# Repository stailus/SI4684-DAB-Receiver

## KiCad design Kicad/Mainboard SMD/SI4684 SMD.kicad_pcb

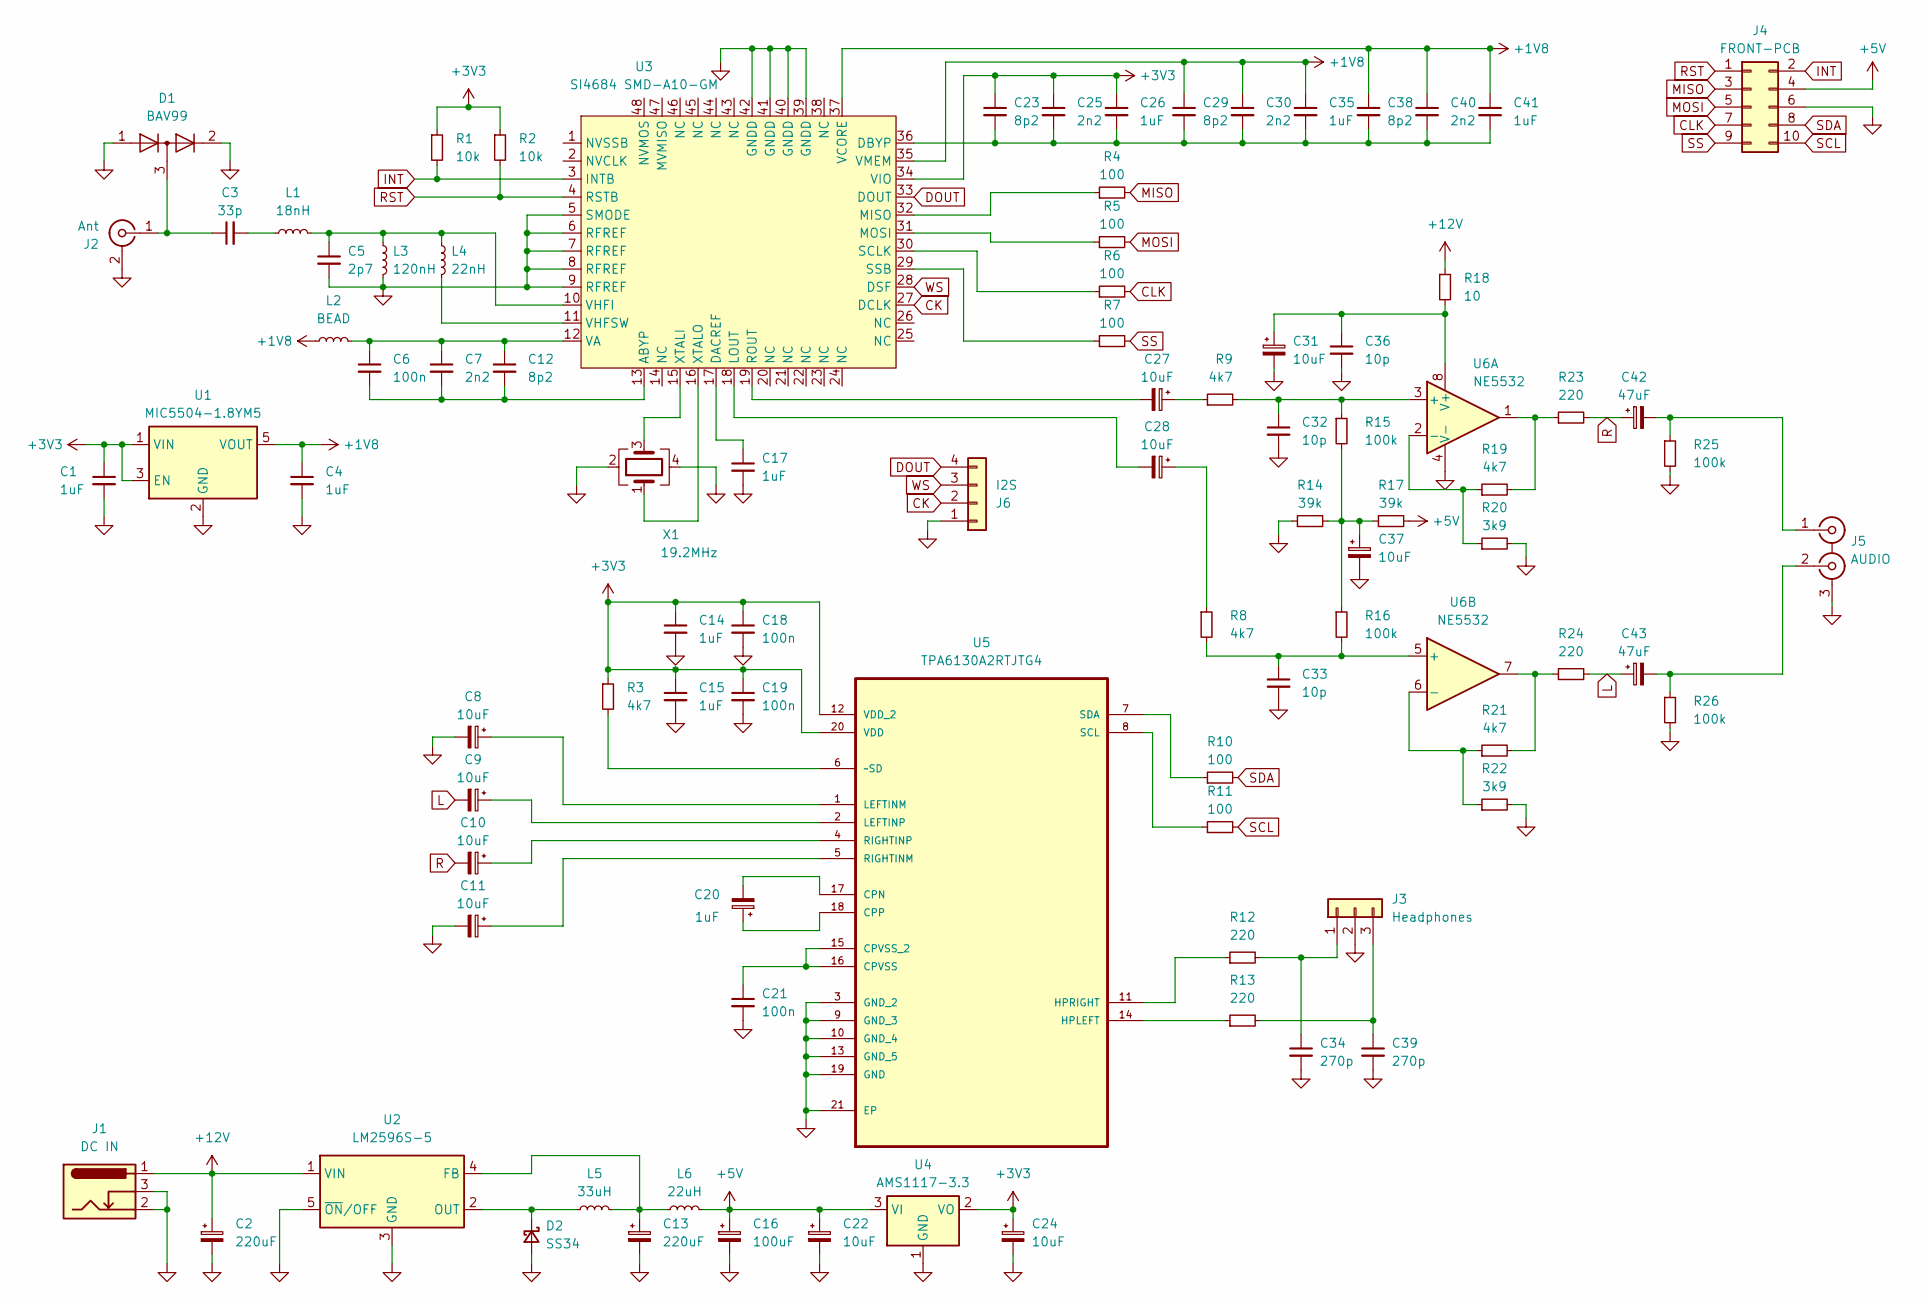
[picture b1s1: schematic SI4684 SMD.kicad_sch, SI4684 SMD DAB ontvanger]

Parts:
C1, C4, C14, C15, C17, C26, C35, C41: 1uF; C_0603_1608Metric
C2, C13: 220uF; CP_Elec_6.3x7.7
C3: 33p; C_0603_1608Metric
C5: 2p7; C_0603_1608Metric
C6, C18, C19, C21: 100n; C_0603_1608Metric
C7, C25, C30, C40: 2n2; C_0603_1608Metric
C8, C9, C10, C11, C22, C24, C27, C28, C31, C37: 10uF; CP_Elec_4x5.4
C12, C23, C29, C38: 8p2; C_0603_1608Metric
C16: 100uF; CP_Elec_6.3x7.7
C20: 1uF; CP_Elec_4x5.4
C32, C33, C36: 10p; C_0603_1608Metric
C34, C39: 270p; C_0603_1608Metric
C42, C43: 47uF; CP_Elec_6.3x5.4
D1: BAV99; SOT-23
D2: SS34; D_SMB
J1: DC IN; BarrelJack_Horizontal
J2: Ant; SMA_Amphenol_132134-16_Vertical
J3: Headphones; JST_PH_B3B-PH-K_1x03_P2.00mm_Vertical
J4: FRONT-PCB; IDC-Header_2x05_P2.54mm_Vertical
J5: AUDIO; FC68405_cinch
J6: I2S; PinHeader_1x04_P2.54mm_Vertical
L1: 18nH; L_0603_1608Metric
L2: BEAD; L_0603_1608Metric
L3: 120nH; L_0603_1608Metric
L4: 22nH; L_0603_1608Metric
L5: 33uH; L_TracoPower_TCK-047_5.2x5.8mm
L6: 22uH; L_TracoPower_TCK-047_5.2x5.8mm
R1, R2: 10k; R_0603_1608Metric
R3, R8, R9, R19, R21: 4k7; R_0603_1608Metric
R4, R5, R6, R7, R10, R11: 100; R_0603_1608Metric
R12, R13, R23, R24: 220; R_0603_1608Metric
R14, R17: 39k; R_0603_1608Metric
R15, R16, R25, R26: 100k; R_0603_1608Metric
R18: 10; R_0603_1608Metric
R20, R22: 3k9; R_0603_1608Metric
U1: MIC5504-1.8YM5; SOT-23-5
U2: LM2596S-5; TO-263-5_TabPin3
U3: SI4684 SMD-A10-GM; QFN-48-1EP_7x7mm_P0.5mm_EP5.3x5.3mm
U4: AMS1117-3.3; SOT-223-3_TabPin2
U5: TPA6130A2RTJTG4; QFN-20-1EP_4x4mm_P0.5mm_EP2.7x2.7mm; MPN TPA6130A2RTJTG4
U6: NE5532; SOIC-8_3.9x4.9mm_P1.27mm
X1: 19.2MHz; Crystal_SMD_3225-4Pin_3.2x2.5mm

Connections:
+1V8: C4.1, C29.1, C30.1, C35.1, C38.1, C40.1, C41.1, L2.1, U1.5 (VOUT), U3.35 (VMEM), U3.37 (VCORE)
+3V3: C1.1, C14.1, C15.1, C18.1, C19.1, C23.1, C24.1, C25.1, C26.1, R1.1, R2.1, R3.1, U1.1 (VIN), U1.3 (EN), U3.34 (VIO), U4.2 (VO), U5.12 (VDD_2), U5.20 (VDD)
+5V: C16.1, C22.1, J4.4, L6.2, R17.2, U4.3 (VI)
+12V: C2.1, J1.1, R18.1, U2.1 (VIN)
CK: J6.2, U3.27 (DCLK)
CLK: J4.7, R6.2
DOUT: J6.4, U3.33 (DOUT)
GND: C1.2, C2.2, C4.2, C5.2, C8.2, C11.2, C13.2, C14.2, C15.2, C16.2, C17.2, C18.2, C19.2, C21.2, C22.2, C24.2, C31.2, C32.2, C33.2, C34.2, C36.2, C37.2, C39.2, D1.1 (K), D1.2 (A), D2.2 (A), J1.2, J1.3, J2.2 (Ext), J3.2, J4.6, J5.3 (EXT), J6.1, L3.2, R14.1, R20.2, R22.2, R25.2, R26.2, U1.2 (GND), U2.3 (GND), U2.5 (~ON/OFF), U3.5 (SMODE), U3.6 (RFREF), U3.7 (RFREF), U3.8 (RFREF), U3.9 (RFREF), U3.39 (GNDD), U3.40 (GNDD), U3.41 (GNDD), U3.42 (GNDD), U3.49 (GND), U4.1 (GND), U5.3 (GND_2), U5.9 (GND_3), U5.10 (GND_4), U5.13 (GND_5), U5.19 (GND), U5.21 (EP), U6.4 (V-), X1.2, X1.4
INT: J4.2, R1.2, U3.3 (INTB)
L: C9.2, C43.1, R24.2
MISO: J4.3, R4.2
MOSI: J4.5, R5.2
unnamed: C3.2, L1.1
unnamed: C27.1, R9.1
unnamed: C28.1, R8.1
unnamed: C37.1, R14.2, R15.2, R16.1, R17.1
unnamed: D2.1 (K), L5.1, U2.2 (OUT)
unnamed: C3.1, D1.3 (K), J2.1 (In)
unnamed: C34.1, J3.1, R12.2
unnamed: C39.1, J3.3, R13.2
unnamed: C42.2, J5.1 (IN1), R25.1
unnamed: C43.2, J5.2 (IN2), R26.1
unnamed: R19.2, R23.1, U6.1
unnamed: R21.2, R24.1, U6.7
unnamed: C13.1, L5.2, L6.1, U2.4 (FB)
unnamed: C6.2, C7.2, C12.2, U3.13 (ABYP)
unnamed: C17.1, U3.17 (DACREF)
unnamed: C23.2, C25.2, C26.2, C29.2, C30.2, C35.2, C38.2, C40.2, C41.2, U3.36 (DBYP)
unnamed: C28.2, U3.18 (LOUT)
unnamed: R4.1, U3.32 (MISO)
unnamed: R5.1, U3.31 (MOSI)
unnamed: C27.2, U3.19 (ROUT)
unnamed: R6.1, U3.30 (SCLK)
unnamed: R7.1, U3.29 (SSB)
unnamed: C6.1, C7.1, C12.1, L2.2, U3.12 (VA)
unnamed: C5.1, L1.2, L3.1, L4.1, U3.10 (VHFI)
unnamed: L4.2, U3.11 (VHFSW)
unnamed: U3.15 (XTALI), X1.3
unnamed: U3.16 (XTALO), X1.1
unnamed: C20.2, U5.17 (CPN)
unnamed: C20.1, U5.18 (CPP)
unnamed: C21.1, U5.15 (CPVSS_2), U5.16 (CPVSS)
unnamed: R13.1, U5.14 (HPLEFT)
unnamed: R12.1, U5.11 (HPRIGHT)
unnamed: C8.1, U5.1 (LEFTINM)
unnamed: C9.1, U5.2 (LEFTINP)
unnamed: C11.1, U5.5 (RIGHTINM)
unnamed: C10.1, U5.4 (RIGHTINP)
unnamed: R11.1, U5.8 (SCL)
unnamed: R10.1, U5.7 (SDA)
unnamed: R3.2, U5.6 (~SD)
unnamed: C32.1, R9.2, R15.1, U6.3 (+)
unnamed: R19.1, R20.1, U6.2 (-)
unnamed: C33.1, R8.2, R16.2, U6.5 (+)
unnamed: R21.1, R22.1, U6.6 (-)
unnamed: C31.1, C36.1, R18.2, U6.8 (V+)
R: C10.2, C42.1, R23.2
RST: J4.1, R2.2, U3.4 (RSTB)
SCL: J4.10, R11.2
SDA: J4.8, R10.2
SS: J4.9, R7.2
WS: J6.3, U3.28 (DSF)

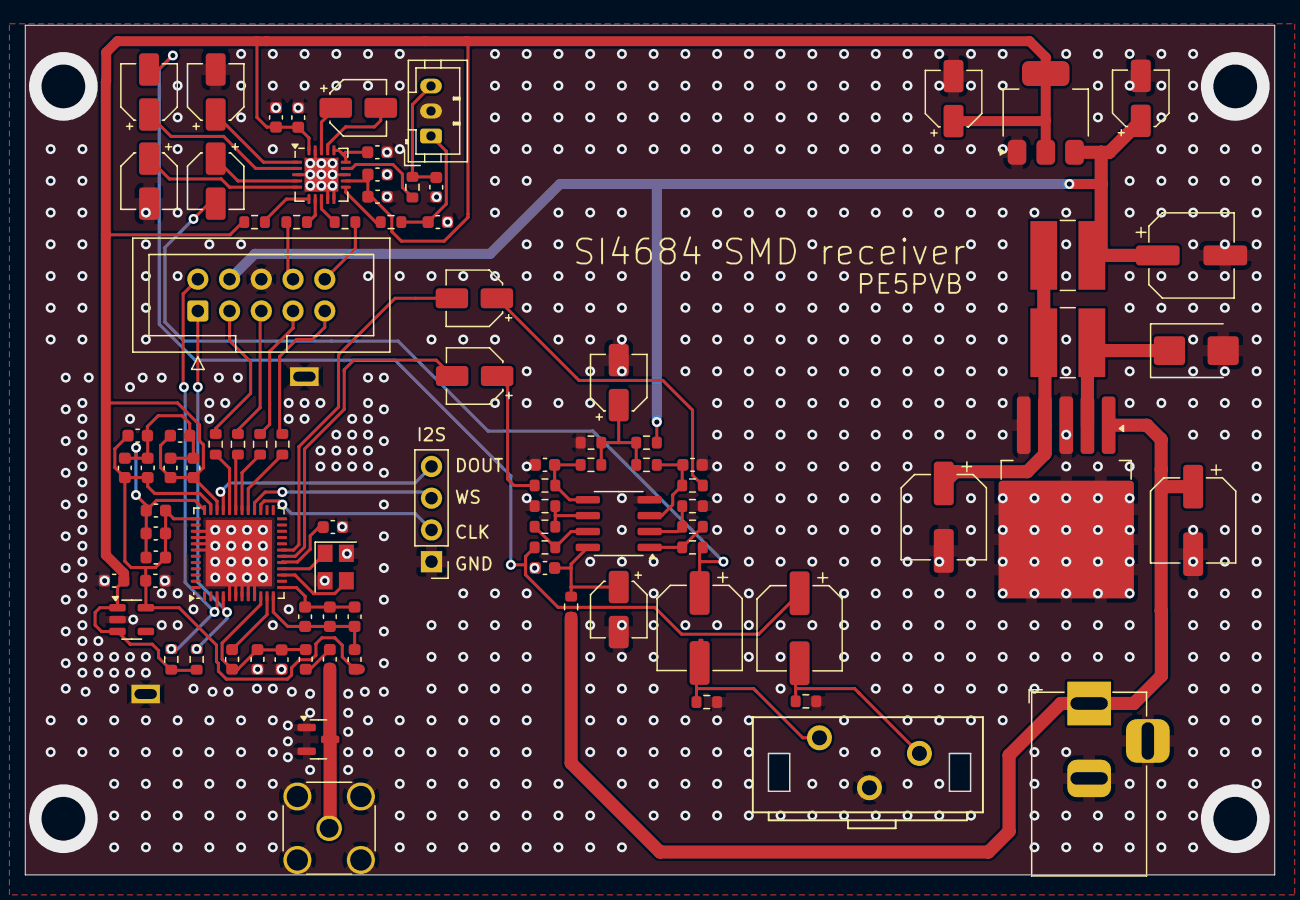
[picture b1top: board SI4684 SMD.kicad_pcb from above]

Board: 2 copper layers, 100.0 x 68.0 mm, 90 parts (0 on the bottom side), 62 nets.

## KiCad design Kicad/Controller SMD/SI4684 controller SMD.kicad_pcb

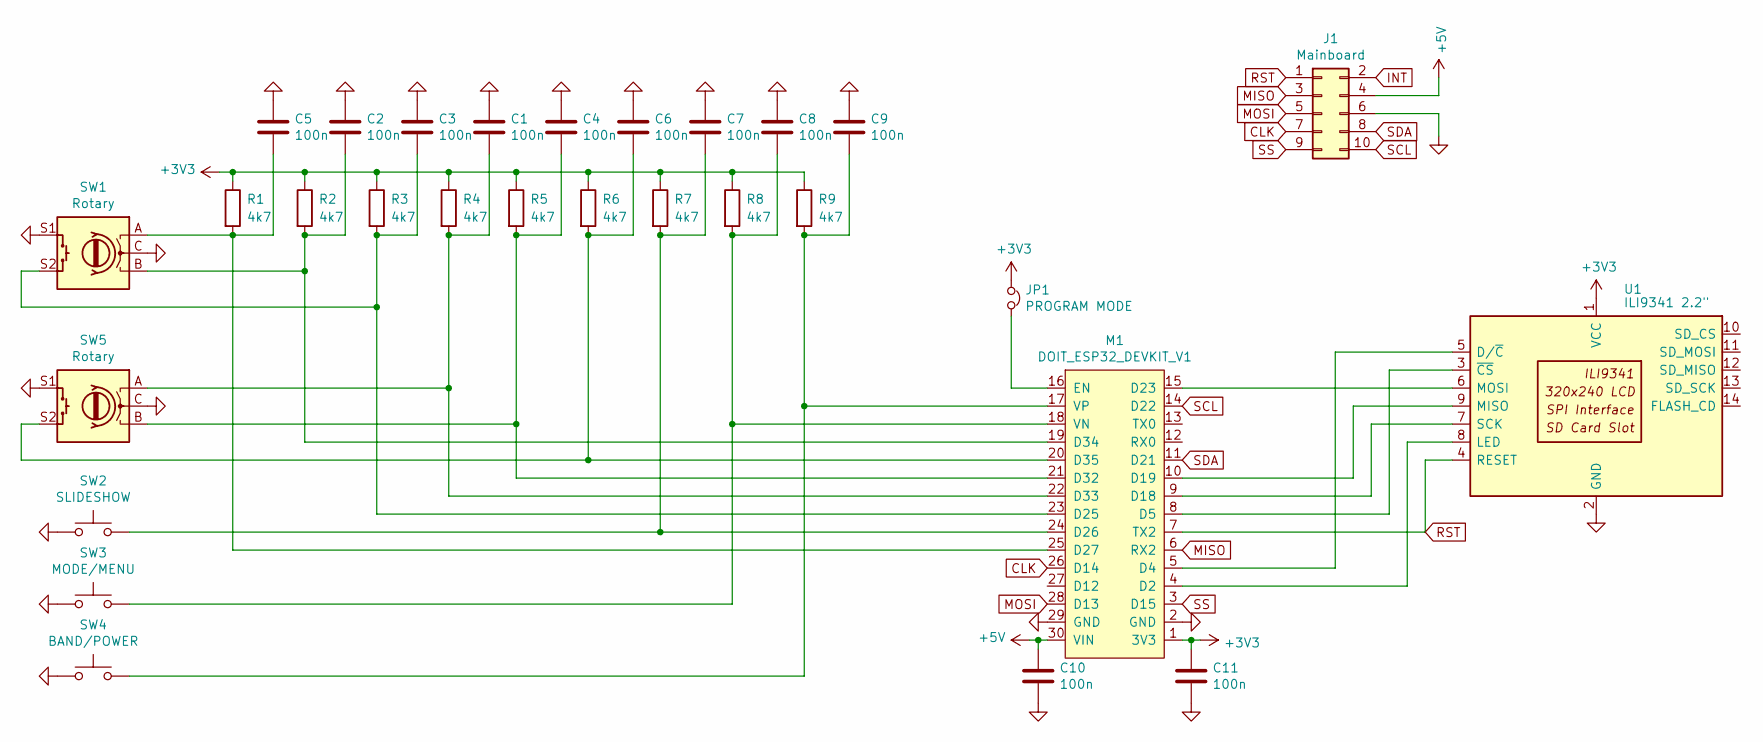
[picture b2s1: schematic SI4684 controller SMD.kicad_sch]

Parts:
C1, C2, C3, C4, C5, C6, C7, C8, C9, C10, C11: 100n; C_0603_1608Metric
J1: Mainboard; IDC-Header_2x05_P2.54mm_Vertical
JP1: PROGRAM MODE; TestPoint_2Pads_Pitch2.54mm_Drill0.8mm
M1: DOIT_ESP32_DEVKIT_V1; ESP32_DOIT_DEVKIT_V1
R1, R2, R3, R4, R5, R6, R7, R8, R9: 4k7; R_0603_1608Metric
SW1, SW5: Rotary; RotaryEncoder_Alps_EC11E-Switch_Vertical_H20mm
SW2: SLIDESHOW; SW_PUSH_6mm_H7.3mm
SW3: MODE/MENU; SW_PUSH_6mm_H7.3mm
SW4: BAND/POWER; SW_PUSH_6mm_H7.3mm
U1: ILI9341 2.2"; CR2013-MI2120

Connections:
+3V3: C11.1, JP1.1, M1.1 (3V3), R1.1, R2.1, R3.1, R4.1, R5.1, R6.1, R7.1, R8.1, R9.1, U1.1 (VCC)
+5V: C10.1, J1.4, M1.30 (VIN)
CLK: J1.7, M1.26 (D14)
GND: C1.1, C2.1, C3.1, C4.1, C5.1, C6.1, C7.1, C8.1, C9.1, C10.2, C11.2, J1.6, M1.2 (GND), M1.29 (GND), SW1.C, SW1.S1, SW2.1, SW3.1, SW4.1, SW5.C, SW5.S1, U1.2 (GND)
INT: J1.2
MISO: J1.3, M1.6 (RX2)
MOSI: J1.5, M1.28 (D13)
unnamed: M1.4 (D2), U1.8 (LED)
unnamed: M1.5 (D4), U1.5 (D/~C)
unnamed: M1.8 (D5), U1.3 (~CS)
unnamed: M1.9 (D18), U1.7 (SCK)
unnamed: M1.10 (D19), U1.9 (MISO)
unnamed: M1.15 (D23), U1.6 (MOSI)
unnamed: C3.2, M1.23 (D25), R3.2, SW1.S2
unnamed: C7.2, M1.24 (D26), R7.2, SW2.2
unnamed: C5.2, M1.25 (D27), R1.2, SW1.A
unnamed: C4.2, M1.21 (D32), R5.2, SW5.B
unnamed: C1.2, M1.22 (D33), R4.2, SW5.A
unnamed: C2.2, M1.19 (D34), R2.2, SW1.B
unnamed: C6.2, M1.20 (D35), R6.2, SW5.S2
unnamed: JP1.2, M1.16 (EN)
unnamed: C8.2, M1.18 (VN), R8.2, SW3.2
unnamed: C9.2, M1.17 (VP), R9.2, SW4.2
RST: J1.1, M1.7 (TX2), U1.4 (RESET)
SCL: J1.10, M1.14 (D22)
SDA: J1.8, M1.11 (D21)
SS: J1.9, M1.3 (D15)

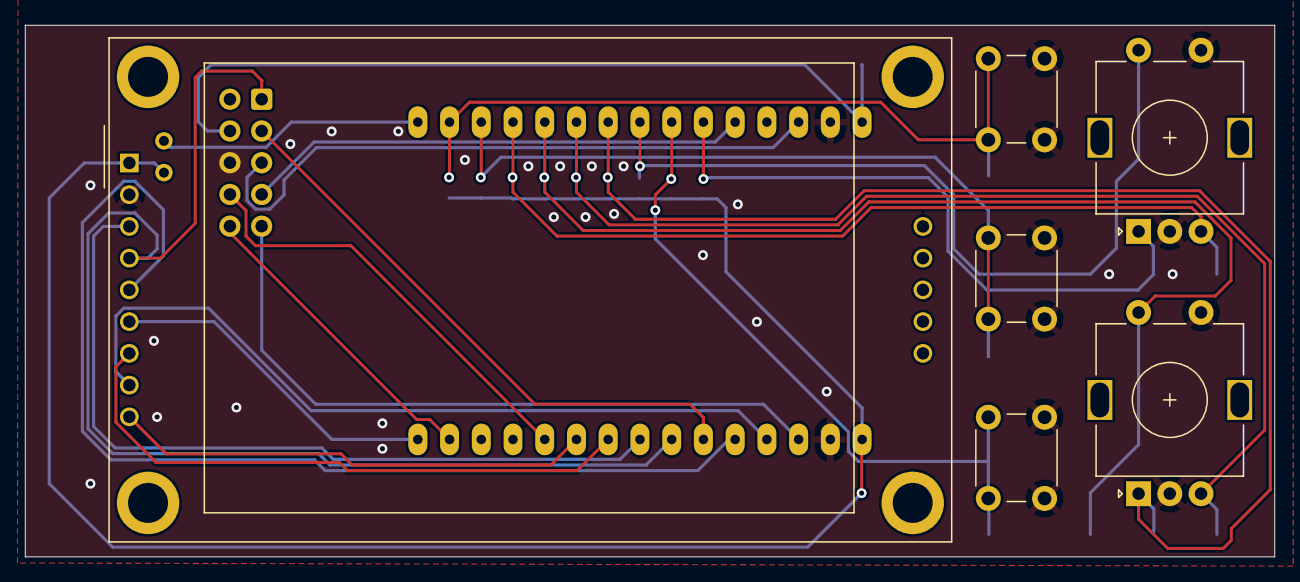
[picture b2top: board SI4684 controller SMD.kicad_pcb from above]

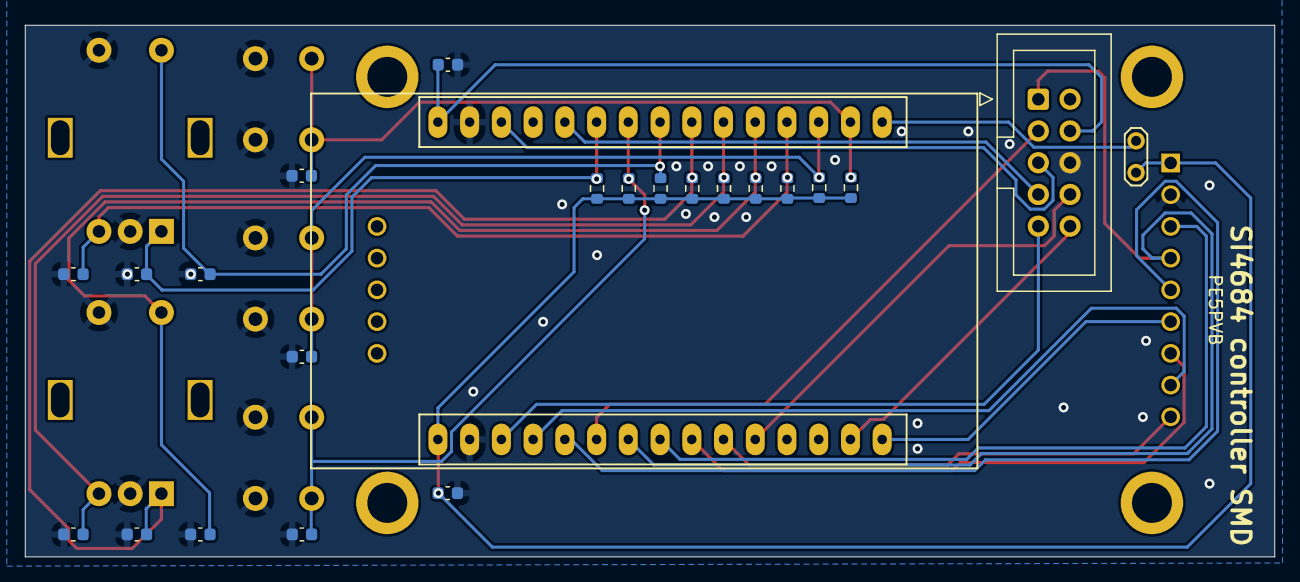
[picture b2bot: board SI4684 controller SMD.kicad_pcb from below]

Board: 2 copper layers, 100.0 x 42.5 mm, 29 parts (23 on the bottom side), 26 nets.

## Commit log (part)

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2025-07-09 Added SMD board Kicad files
2025-12-29 Fixed problem with compiling slideshow
2026-01-07 Fixed date/time parsing
2026-01-07 Fixed date/time detection
    Added Partitions file, choose "custom" when compiling with latest boardmanager
2026-01-10 Added Polish language
2026-01-11 Addes support for 16-bit UTF8 conversion (thanks Andrzej Jeroszuk)
2026-01-15 Improvement of channellist parsing
2026-01-15 Sometimes tuning failed
2026-01-15 Added Service ECC detection
2026-01-15 Old WiFi residu erased
2026-01-16 Faster assembly of slideshow images
2026-01-16 Update partitions file
2026-01-16 Removed tft_espi from API. Doesn't belong there
2026-01-17 Fixed problem for compiling with Arduino IDE
2026-01-24 Remove slideshow buffer when size mismatches
2026-01-24 Added missing ASCII
2026-01-24 Speed optimise on weak signal
2026-01-24 Default volume value after reset should be 100%
2026-01-29 Fixed fading error on failing slideshow
2026-02-09 Added support for progressive JPG view (limited to low resolution!)
2026-02-09 Improved LNA configuration (thanks Bernhard)
2026-02-09 Fix EID and Ensemblename when EID ends with 0
2026-02-09 Fixed problem with ECC display
2026-02-09 Undo some buggy changes
2026-02-11 Improved slideshow assembly speed
2026-02-11 Versioning
2026-02-14 Background of transparant PNG fixed
2026-02-14 White background on transparant PNG
2026-02-14 MOT header detection: increase byte_count threshold from 65 to 200.
2026-02-15 Added Romanian language
2026-02-15 Better support for progressive JPG
2026-02-16 JPEG decoder compatibility update
2026-02-18 More work on slideshow parser
2026-02-19 Added base64 to debug
2026-02-19 Added debug info
